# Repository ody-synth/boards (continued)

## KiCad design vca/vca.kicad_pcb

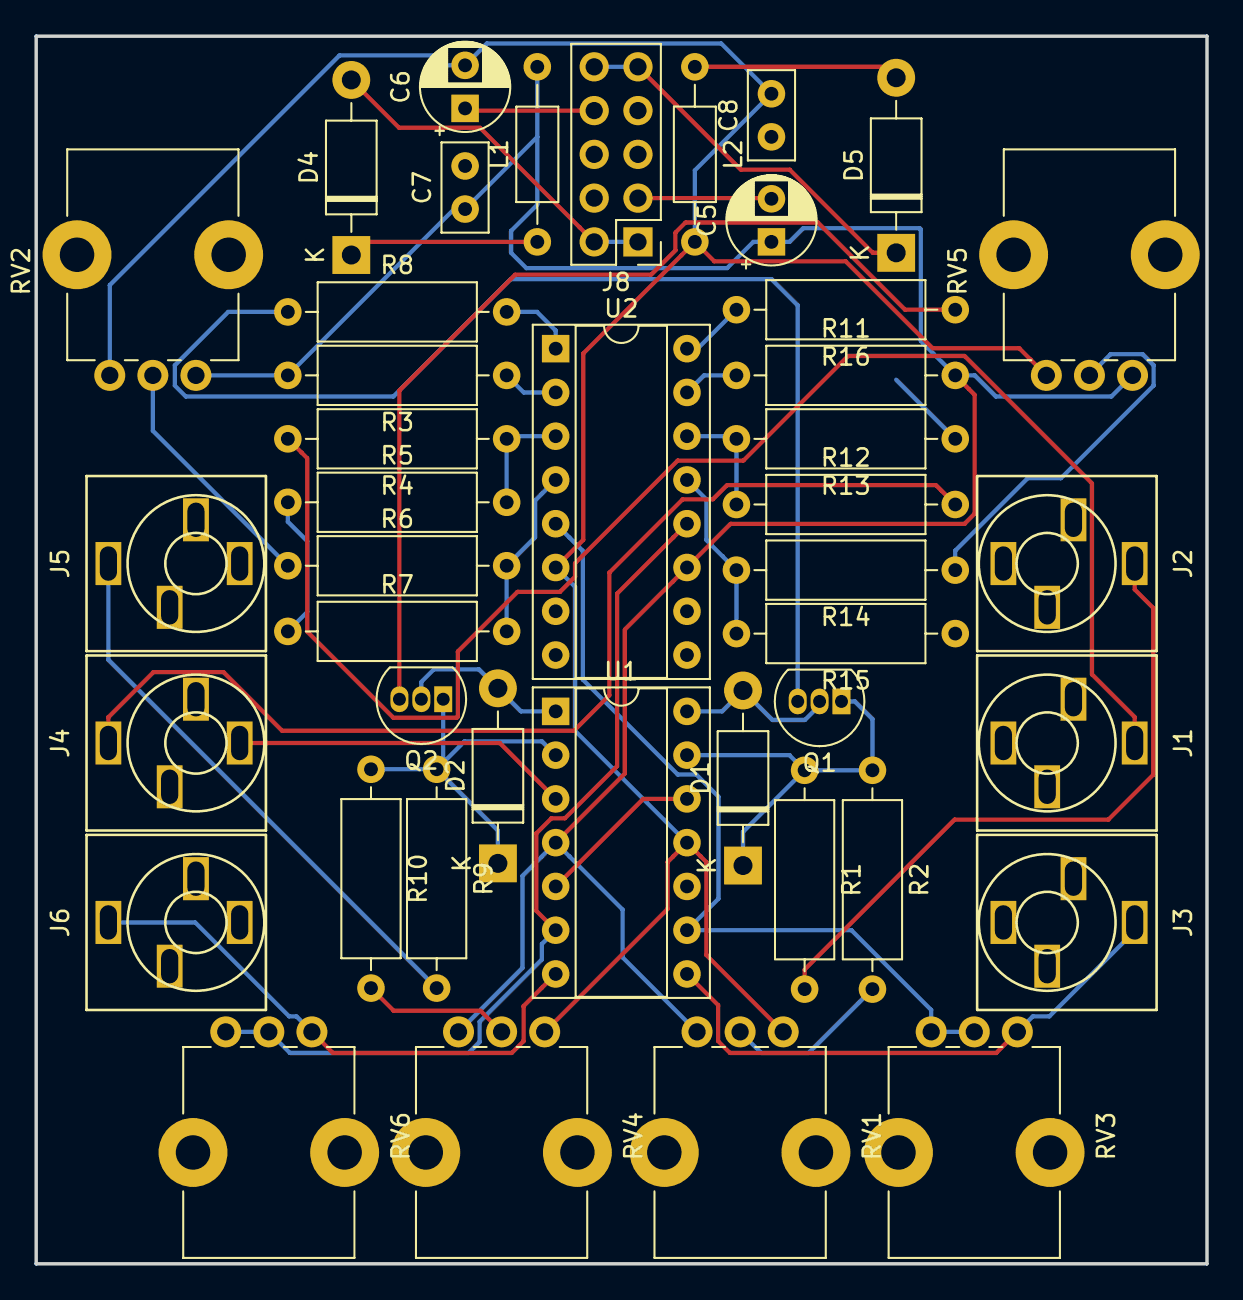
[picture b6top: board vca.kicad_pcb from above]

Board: 2 copper layers, 67.9 x 71.2 mm, 43 parts (0 on the bottom side), 33 nets.

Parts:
C5, C6: 10uF; CP_Radial_D5.0mm_P2.50mm
C7, C8: 100nF; C_Disc_D5.0mm_W2.5mm_P2.50mm
D1, D2: 1N4006; D_DO-41_SOD81_P10.16mm_Horizontal
D4, D5: 1N4007; D_DO-41_SOD81_P10.16mm_Horizontal
J1: IN1; jack_audio
J2: VC1; jack_audio
J3: OUT1; jack_audio
J4: IN2; jack_audio
J5: VC2; jack_audio
J6: OUT2; jack_audio
J8: Conn_02x05_Odd_Even; PinHeader_2x05_P2.54mm_Vertical
L1, L2: 22uH; L_Axial_L5.3mm_D2.2mm_P10.16mm_Horizontal_Vishay_IM-1
Q1, Q2: 2N3906; TO-92_Inline
R1, R9: 22K; R_Axial_DIN0309_L9.0mm_D3.2mm_P12.70mm_Horizontal
R2, R5, R7, R8, R10, R13, R15, R16: 10K; R_Axial_DIN0309_L9.0mm_D3.2mm_P12.70mm_Horizontal
R3, R11: 15K; R_Axial_DIN0309_L9.0mm_D3.2mm_P12.70mm_Horizontal
R4, R12: 100K; R_Axial_DIN0309_L9.0mm_D3.2mm_P12.70mm_Horizontal
R6, R14: 1M; R_Axial_DIN0309_L9.0mm_D3.2mm_P12.70mm_Horizontal
RV1, RV4: 10K; Potentiometer_Bourns_PTV09A-1_Single_Vertical
RV2, RV5: 100K; Potentiometer_Bourns_PTV09A-1_Single_Vertical
RV3, RV6: 60K; Potentiometer_Bourns_PTV09A-1_Single_Vertical
U1: TL074; DIP-14_W7.62mm_Socket
U2: LM13600; DIP-16_W7.62mm_Socket

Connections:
12VC: D4.2, J8.1, J8.2
12V_: C5.1, C7.1, L1.2, R3.2, R11.2, RV1.1, RV2.1, RV4.1, RV5.1, U1.4, U2.11
-12VC: D5.1, J8.9, J8.10
-12V_: C6.2, C8.2, L2.2, RV1.3, RV2.3, RV4.3, RV5.3, U1.11, U2.6
/EURORACKPIN/12Vto5V: D4.1, L1.1
GND: C5.2, C6.1, C7.2, C8.1, J1.S, J2.S, J3.S, J4.S, J5.S, J6.S, J8.3, J8.4, J8.5, J8.6, J8.7, J8.8, R5.1, R7.1, R13.1, R15.1, U1.3, U1.5, U1.10, U1.12
unnamed: D1.1, Q1.1, R1.1, R2.1, U1.13
unnamed: D1.2, Q1.2, U1.14
unnamed: D2.1, Q2.1, R9.1, R10.1, U1.2
unnamed: D2.2, Q2.2, U1.1
unnamed: D5.2, L2.1
unnamed: J1.T, R4.2
unnamed: J2.T, R1.2
unnamed: J3.T, RV3.3, U1.8
unnamed: J4.T, R12.2
unnamed: J5.T, R9.2
unnamed: J6.T, RV6.3, U1.7
unnamed: Q1.3, R8.1
unnamed: Q2.3, R16.1
unnamed: R2.2, RV1.2
unnamed: R3.1, U2.2
unnamed: R4.1, R5.2, U2.3
unnamed: R6.1, RV2.2
unnamed: R6.2, R7.2, U2.4
unnamed: R8.2, U2.1
unnamed: R10.2, RV4.2
unnamed: R11.1, U2.15
unnamed: R12.1, R13.2, U2.14
unnamed: R14.1, RV5.2
unnamed: R14.2, R15.2, U2.13
unnamed: R16.2, U2.16
unnamed: RV3.1, RV3.2, U1.9, U2.5
unnamed: RV6.1, RV6.2, U1.6, U2.12

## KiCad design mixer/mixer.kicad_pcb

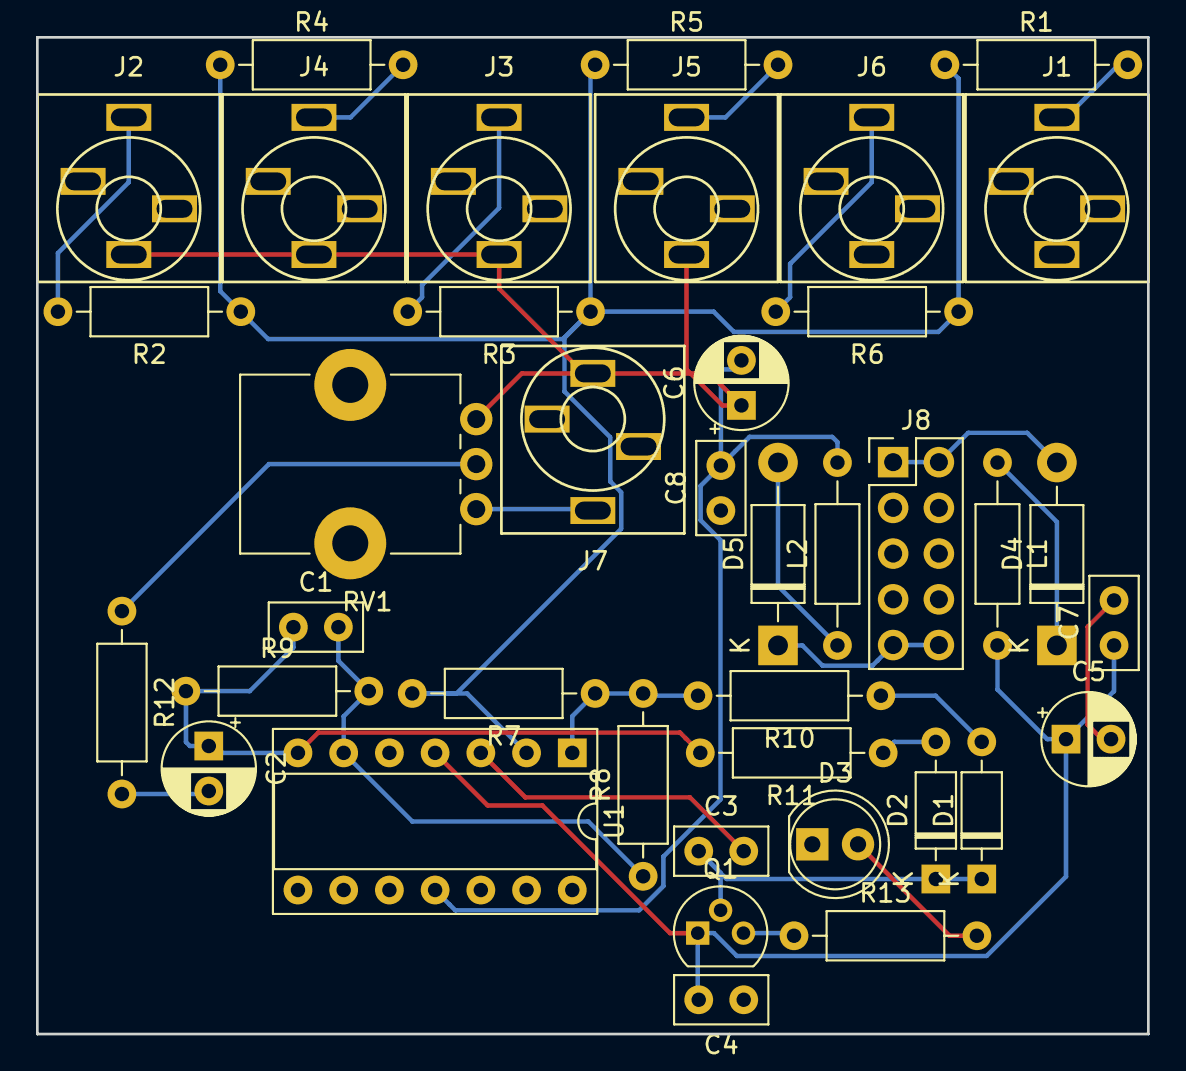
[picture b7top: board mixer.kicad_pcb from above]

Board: 2 copper layers, 61.7 x 55.4 mm, 39 parts (0 on the bottom side), 25 nets.

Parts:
C1: 22pF; C_Disc_D5.0mm_W2.5mm_P2.50mm
C2: 4u7; CP_Radial_D5.0mm_P2.50mm
C3, C4: 100n; C_Disc_D5.0mm_W2.5mm_P2.50mm
C5, C6: 10uF; CP_Radial_D5.0mm_P2.50mm
C7, C8: 100nF; C_Disc_D5.0mm_W2.5mm_P2.50mm
D1, D2: 1N4148; D_DO-35_SOD27_P7.62mm_Horizontal
D3: LED; LED_D5.0mm
D4, D5: 1N4007; D_DO-41_SOD81_P10.16mm_Horizontal
J1, J2, J3, J4, J5, J6: IN1; jack_audio
J7: OUT1; jack_audio
J8: Conn_02x05_Odd_Even; PinHeader_2x05_P2.54mm_Vertical
L1, L2: 22uH; L_Axial_L5.3mm_D2.2mm_P10.16mm_Horizontal_Vishay_IM-1
Q1: BC546a; TO-92
R1, R2, R3, R4, R5, R6, R7, R8, R9: 47k; R_Axial_DIN0207_L6.3mm_D2.5mm_P10.16mm_Horizontal
R10, R11: 8k2; R_Axial_DIN0207_L6.3mm_D2.5mm_P10.16mm_Horizontal
R12: 470; R_Axial_DIN0207_L6.3mm_D2.5mm_P10.16mm_Horizontal
R13: 500; R_Axial_DIN0207_L6.3mm_D2.5mm_P10.16mm_Horizontal
RV1: 100k; Potentiometer_Bourns_PTV09A-1_Single_Vertical
U1: TL074; DIP-14_W7.62mm_Socket

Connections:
12V: C4.2, C5.1, C7.1, L1.2, Q1.1, U1.4
12VC: D4.2, J8.1, J8.2
-12V: C6.2, C8.2, L2.2, U1.11
-12VC: D5.1, J8.9, J8.10
/EURORACKPIN/12Vto5V: D4.1, L1.1
GND: C3.2, C4.1, C5.2, C6.1, C7.2, C8.1, D3.1, J1.S, J2.S, J3.S, J4.S, J5.S, J6.S, J7.S, J8.3, J8.4, J8.5, J8.6, J8.7, J8.8, RV1.1, U1.3, U1.5
unnamed: C1.1, C2.1, R9.1, R11.2, U1.7
unnamed: C1.2, R8.1, R9.2, U1.6
unnamed: C2.2, R12.2
unnamed: C3.1, D1.1, D2.1, Q1.2
unnamed: D1.2, R10.1
unnamed: D2.2, R11.1
unnamed: D3.2, R13.2
unnamed: D5.2, L2.1
unnamed: J1.T, R1.2
unnamed: J2.T, R2.2
unnamed: J3.T, R3.2
unnamed: J4.T, R4.2
unnamed: J5.T, R5.2
unnamed: J6.T, R6.2
unnamed: J7.T, RV1.3
unnamed: Q1.3, R13.1
unnamed: R7.1, R8.2, R10.2, U1.1
unnamed: R12.1, RV1.2
mixed: R1.1, R2.1, R3.1, R4.1, R5.1, R6.1, R7.2, U1.2

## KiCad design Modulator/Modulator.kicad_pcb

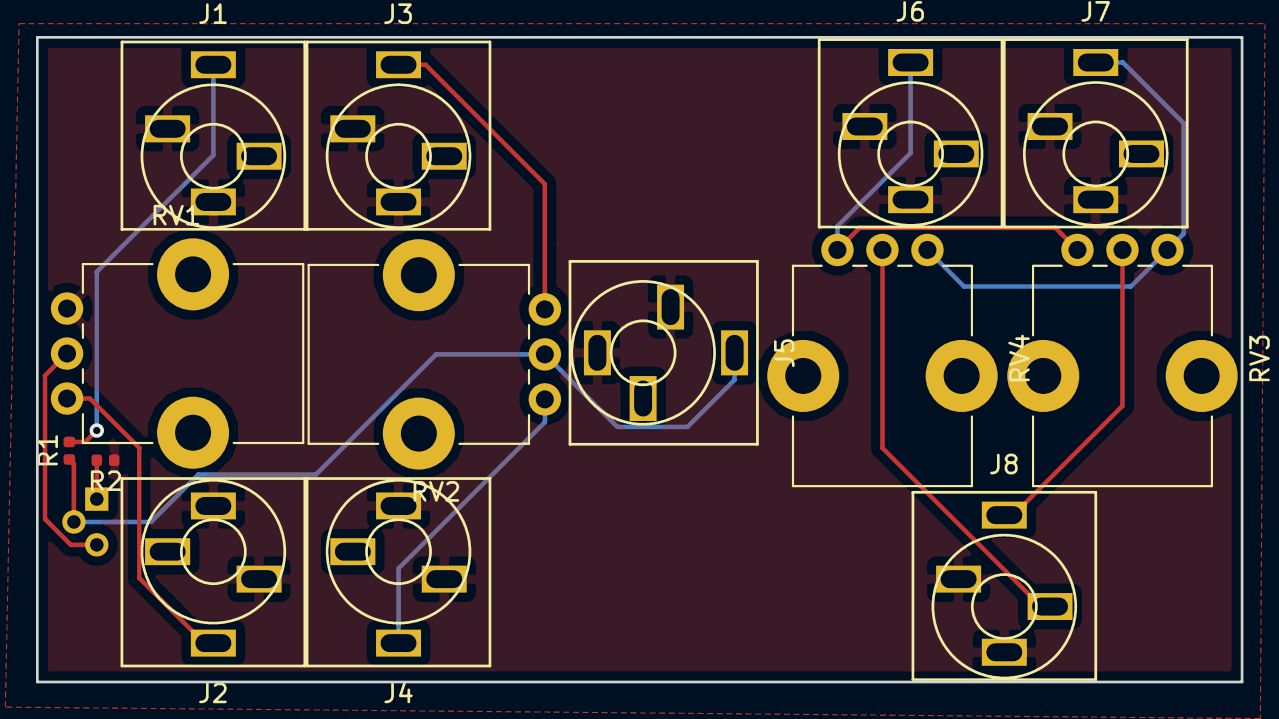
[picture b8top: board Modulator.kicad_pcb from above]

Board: 2 copper layers, 66.9 x 35.8 mm, 15 parts (1 on the bottom side), 12 nets.

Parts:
J1, J3: CARRIER1; jack_audio
J2, J4: MESSAGE2; jack_audio
J5, J8: OUT1; jack_audio
J6: L; jack_audio
J7: R; jack_audio
Q1: NFET; TO-92
R1: 1K; R_0402_1005Metric
R2: 10K; R_0402_1005Metric
RV1, RV3, RV4: 20k; Potentiometer_Bourns_PTV09A-1_Single_Vertical
RV2: 100k; Potentiometer_Bourns_PTV09A-1_Single_Vertical

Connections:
GND: J1.G, J1.S, J2.G, J2.S, J3.G, J3.S, J4.G, J4.S, J5.G, J5.S, J6.G, J6.S, J7.G, J7.S, J8.G, J8.S, R2.1, RV1.3
L: J8.T, RV3.2
unnamed: J1.T, R1.2
unnamed: J2.T, RV1.1
unnamed: J3.T, RV2.1
unnamed: J4.T, RV2.3
unnamed: J6.T, RV3.1, RV4.1
unnamed: J7.T, RV3.3, RV4.3
unnamed: Q1.1, R2.2
unnamed: Q1.3, RV1.2
R: J8.R, RV4.2
VOUT: J5.T, Q1.2, R1.1, RV2.2

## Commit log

2019-02-13 created project
2019-02-13 Components to check
2019-02-13 Updated midi input and PIC
2019-02-13 Updated jacks and outputs
2019-02-14 Updated wave generator pcbs
2019-02-15 Continued PCB wave
2019-02-15 Wave gerber panelized
2019-02-15 3D rendering
2019-02-19 VCO began CEM3340 board
2019-02-20 VCO board
2019-02-22 Moved vco project
2019-03-13 Added mixer from ponyo:syntherjack
2019-03-14 Finished dual linear vca
2019-03-15 Gerber mixer
2019-03-16 Started ADSR envelop generator
2019-03-19 8Step sequencer finished with pic
2019-03-19 Added gate to sequencer
2019-03-25 Began plaits from mutable instruments
2019-03-26 Modified the eurorackpin schematic and cleaned up
2019-03-26 Added yarns midi eurorack
2019-03-26 Continued yarns board
2021-03-12 Added vcos infos
